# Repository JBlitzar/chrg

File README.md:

# chrg

chrg is a usbc charging hub. You can use it to charge your devices! It uses a CH224K PD sink as input, and then 4xIP6518 PD source controllers as output. 

Thanks to the IP6518, it should support:

 - 45W
 - USB-C Power Delivery
 - BC1.2 charging
 - Qualcomm QC2.0 and 3.0 charging
 - Apple, Huawei, Samsung, and Spreadtrum fast charging protocols
   - I don't have any huawei phones, but maybe you do! You can use chrg to charge them.

 Of course, YMMV when plugging in multiple devices. It's mostly bottlenecked by the wattage of your upstream brick (or alternatively 45W as the ip6518 spec says).

 ### Why I made this project

 I made this project because I like doing USB projects, and after making a [USB *data* hub](https://github.com/jblitzar/uhub), I thought it would be cool to make a *charging* hub. Plus, this way I can plug in one brick and charge my phone and headphones at the same time. I also think it's cool and was a way to learn a new chip (IP6518).

## Schematic

Root schematic:

Schematic for the `out` block:

## PCB

[View on Kicanvas](https://kicanvas.org/?repo=https%3A%2F%2Fgithub.com%2FJBlitzar%2Fchrg%2Ftree%2Fmain%2FPCB%2Fchrg)

## CAD

[Onshape link](https://cad.onshape.com/documents/9567810a3a804626e0b9bd5e/w/546991992eff6807c34164d7/e/56ab2d679f572004bdd7b5fb?renderMode=0&uiState=6a89de2326941f564e9ba193)

Assembly: [CAD/chrg_assembly.step](CAD/chrg_assembly.step)

Or just check the [CAD folder](CAD/)

PCB is held in place with the mounting holes

## How to use

### Assembly

Print chrg_case.step instead and slide it in from the side, like so:

Then the pins should keep it secure. 

### Usage

Plug a usbc laptop charger into the side port. Then, charge your devices from the front ports!

## Testimonials

Don't just take it from me! Hear what users are saying about chrg

> *What are you making...*

> *this shit is not passing tsa bro*

> *Scary*

> *CHAAARGGGGEEEEEEE!!!!!!!!!!!!!!*

## BOM

|Item                                              |link                               |Cost|Notes           |
|--------------------------------------------------|-----------------------------------|----|----------------|
|5x PCB (moq)                                      |N/A                                |4   |JLC             |
|2x PCBA (moq)                                     |N/A                                |45.87|JLC             |
|JLC shipping + taxes                              |N/A                                |8   |                |
|1x case                                           |N/A                                |0   |I can print this myself|
|Total                                             |N/A                                |57.87|                |

### Fabrication BOM

Other fabrication outputs at [PCB/chrg/production](PCB/chrg/production)

|Designator                                        |Footprint                          |Quantity|Value           |LCSC Part #|Link|
|--------------------------------------------------|-----------------------------------|--------|----------------|-----------|----|
|C1                                                |C0603                              |1       |1uf             |C15849     |[link](https://www.lcsc.com/product-detail/C15849.html)|
|C10, C11, C12, C13, C2, C3, C4, C5, C6, C7, C8, C9|C0603                              |12      |22uF            |C59461     |[link](https://www.lcsc.com/product-detail/C59461.html)|
|C14                                               |C1206                              |1       |100uF           |C15008     |[link](https://www.lcsc.com/product-detail/C15008.html)|
|C32, C34, C39, C41, C46, C48, C53, C55            |C0402                              |8       |100nF           |C1525      |[link](https://www.lcsc.com/product-detail/C1525.html)|
|C33, C40, C47, C54                                |C0402                              |4       |1nF             |C1523      |[link](https://www.lcsc.com/product-detail/C1523.html)|
|F1                                                |FUSE-SMD_2410-T4A-125V             |1       |4A fuse         |C5220739   |[link](https://www.lcsc.com/product-detail/C5220739.html)|
|L1, L2, L3, L4                                    |IND-SMD_L14.4-W12.8                |4       |SLO1350H220MTT  |C364085    |[link](https://www.lcsc.com/product-detail/C364085.html)|
|LED1, LED6, LED7, LED8, LED9                      |LED0805-R-RD                       |5       |0805G           |C2297      |[link](https://www.lcsc.com/product-detail/C2297.html)|
|R16, R17, R19, R20, R21, R22, R23, R25, R26       |R0402                              |9       |3.3kΩ           |C25890     |[link](https://www.lcsc.com/product-detail/C25890.html)|
|R2                                                |R0402                              |1       |1k              |C11702     |[link](https://www.lcsc.com/product-detail/C11702.html)|
|R3, R4, R5, R6                                    |R0603                              |4       |2Ω              |C22977     |[link](https://www.lcsc.com/product-detail/C22977.html)|
|U1                                                |R0805                              |1       |10k             |C17414     |[link](https://www.lcsc.com/product-detail/C17414.html)|
|U11, U13, U15, U17                                |QFN-24_L4.0-W4.0-P0.50-BL-EP2.6    |4       |IP6518          |C181688    |[link](https://www.lcsc.com/product-detail/C181688.html)|
|U2                                                |ESSOP-10_L4.9-W3.9-P1.0-LS6.0-TL-EP|1       |CH224K          |C970725    |[link](https://www.lcsc.com/product-detail/C970725.html)|
|USB1, USB10, USB11, USB12, USB9                   |USB-C-SMD_TYPE-C-16PIN-2MD-073     |5       |TYPE-C 16PIN 2MD|C2765186   |[link](https://www.lcsc.com/product-detail/C2765186.html)|

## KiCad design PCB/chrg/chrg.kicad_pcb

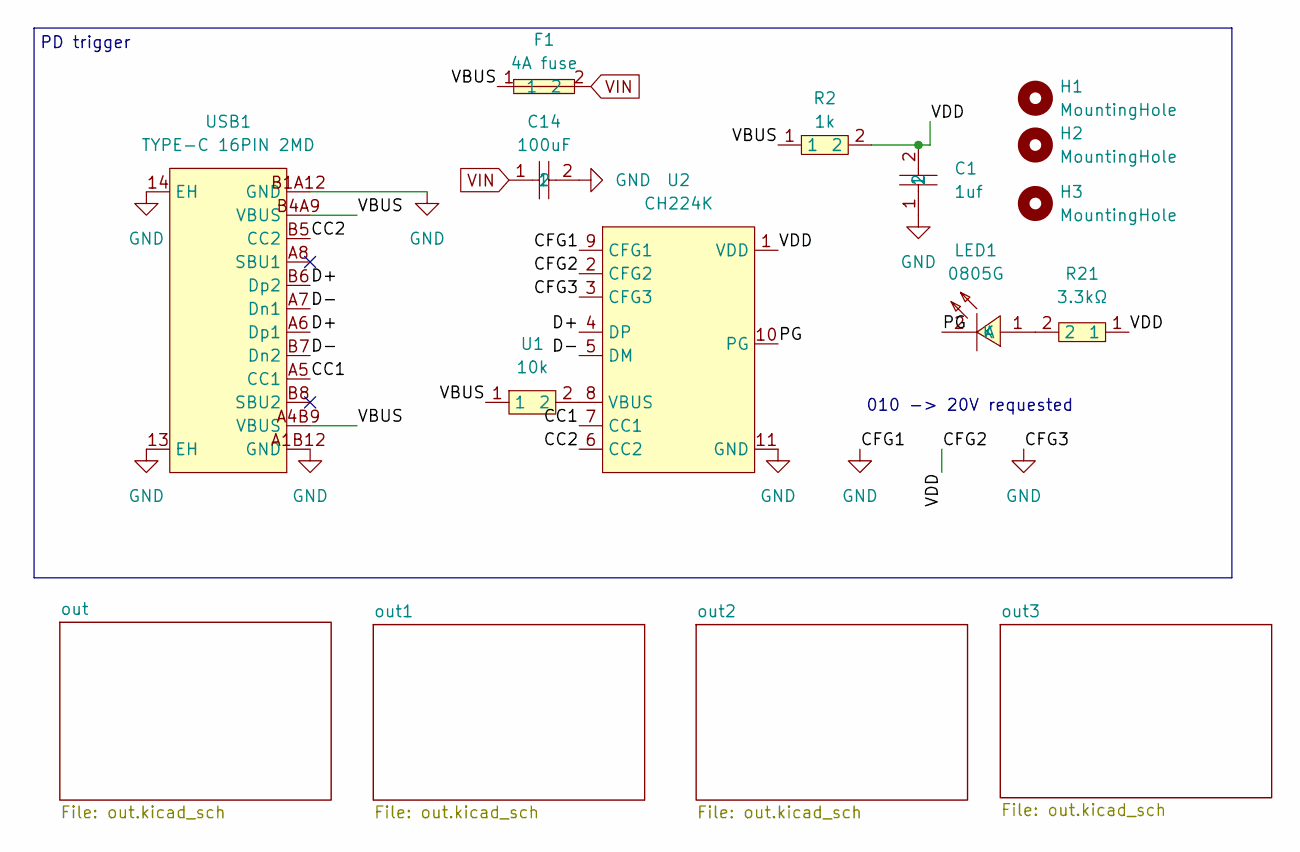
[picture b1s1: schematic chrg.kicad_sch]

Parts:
C1: 1uf; C0603; MPN CL10A105KB8NNNC; LCSC Part C15849
C14: 100uF; C1206; MPN CL31A107MQHNNNE; LCSC Part C15008
F1: 4A fuse; FUSE-SMD_2410-T4A-125V; MPN 2410 T4A/125V; LCSC Part C5220739
H1, H2, H3: MountingHole; MountingHole_2.2mm_M2
LED1: 0805G; LED0805-R-RD; MPN KT-0805G; LCSC Part C2297
R2: 1k; R0402; MPN 0402WGF1001TCE; LCSC Part C11702
R21: 3.3kΩ; R0402; MPN 0402WGF3301TCE; LCSC Part C25890
U1: 10k; R0805; MPN 0805W8F1002T5E; LCSC Part C17414
U2: CH224K; ESSOP-10_L4.9-W3.9-P1.0-LS6.0-TL-EP; MPN CH224K; LCSC Part C970725
USB1: TYPE-C 16PIN 2MD; USB-C-SMD_TYPE-C-16PIN-2MD-073; MPN TYPE-C 16PIN 2MD(073); LCSC Part C2765186

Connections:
/CC1: U2.7 (CC1), USB1.A5 (CC1)
/CC2: U2.6 (CC2), USB1.B5 (CC2)
/CFG2: C1.2, R2.2, R21.1, U2.1 (VDD), U2.2 (CFG2)
/D+: U2.4 (DP), USB1.A6 (Dp1), USB1.B6 (Dp2)
/D-: U2.5 (DM), USB1.A7 (Dn1), USB1.B7 (Dn2)
/PG: LED1.2 (K), U2.10 (PG)
/VBUS: F1.1, R2.1, U1.1, USB1.A4B9 (VBUS), USB1.B4A9 (VBUS)
GND: C1.1, C14.2, U2.3 (CFG3), U2.9 (CFG1), U2.11 (GND), USB1.13 (EH), USB1.14 (EH), USB1.A1B12 (GND), USB1.B1A12 (GND); also elsewhere on the board
unnamed: LED1.1 (A), R21.2
unnamed: U1.2, U2.8 (VBUS)
VIN: C14.1, F1.2; also elsewhere on the board

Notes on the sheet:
PD trigger
010 -> 20V requested

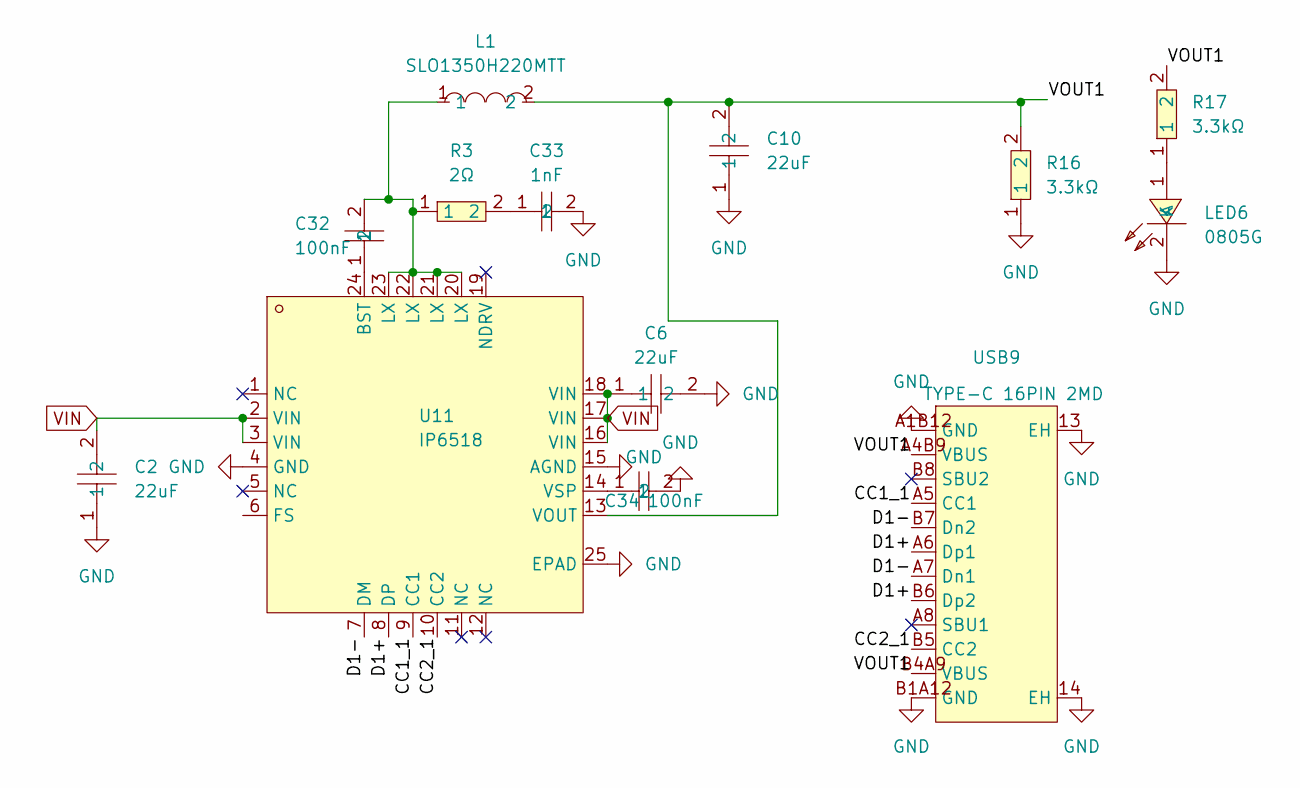
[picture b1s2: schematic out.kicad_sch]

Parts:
C2, C6, C10: 22uF; C0603; MPN CL10A226MQ8NRNC; LCSC Part C59461
C32, C34: 100nF; C0402; MPN CL05B104KO5NNNC; LCSC Part C1525
C33: 1nF; C0402; MPN 0402B102K500NT; LCSC Part C1523
L1: SLO1350H220MTT; IND-SMD_L14.4-W12.8; MPN SLO1350H220MTT; LCSC Part C364085
LED6: 0805G; LED0805-R-RD; MPN KT-0805G; LCSC Part C2297
R3: 2Ω; R0603; MPN 0603WAF200KT5E; LCSC Part C22977
R16, R17: 3.3kΩ; R0402; MPN 0402WGF3301TCE; LCSC Part C25890
U11: IP6518; QFN-24_L4.0-W4.0-P0.50-BL-EP2.6; MPN IP6518; LCSC Part C181688
USB9: TYPE-C 16PIN 2MD; USB-C-SMD_TYPE-C-16PIN-2MD-073; MPN TYPE-C 16PIN 2MD(073); LCSC Part C2765186

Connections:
/out/CC1_1: U11.9 (CC1), USB9.A5 (CC1)
/out/CC2_1: U11.10 (CC2), USB9.B5 (CC2)
/out/D1+: U11.8 (DP), USB9.A6 (Dp1), USB9.B6 (Dp2)
/out/D1-: U11.7 (DM), USB9.A7 (Dn1), USB9.B7 (Dn2)
/out/VOUT1: C10.2, L1.2, R16.2, R17.2, U11.13 (VOUT), USB9.A4B9 (VBUS), USB9.B4A9 (VBUS)
GND: C2.1, C6.2, C10.1, C33.2, C34.2, LED6.2 (K), R16.1, U11.4 (GND), U11.15 (AGND), U11.25 (EPAD), USB9.13 (EH), USB9.14 (EH), USB9.A1B12 (GND), USB9.B1A12 (GND); also elsewhere on the board
unnamed: C32.2, L1.1, R3.1, U11.20 (LX), U11.21 (LX), U11.22 (LX), U11.23 (LX)
unnamed: C33.1, R3.2
unnamed: LED6.1 (A), R17.1
unnamed: C32.1, U11.24 (BST)
unnamed: C34.1, U11.14 (VSP)
VIN: C2.2, C6.1, U11.2 (VIN), U11.3 (VIN), U11.16 (VIN), U11.17 (VIN), U11.18 (VIN); also elsewhere on the board

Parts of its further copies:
C3, C4, C5, C7, C8, C9, C11, C12, C13: 22uF; C0603; MPN CL10A226MQ8NRNC; LCSC Part C59461
C39, C41, C46, C48, C53, C55: 100nF; C0402; MPN CL05B104KO5NNNC; LCSC Part C1525
C40, C47, C54: 1nF; C0402; MPN 0402B102K500NT; LCSC Part C1523
L2, L3, L4: SLO1350H220MTT; IND-SMD_L14.4-W12.8; MPN SLO1350H220MTT; LCSC Part C364085
LED7, LED8, LED9: 0805G; LED0805-R-RD; MPN KT-0805G; LCSC Part C2297
R4, R5, R6: 2Ω; R0603; MPN 0603WAF200KT5E; LCSC Part C22977
R19, R20, R22, R23, R25, R26: 3.3kΩ; R0402; MPN 0402WGF3301TCE; LCSC Part C25890
U13, U15, U17: IP6518; QFN-24_L4.0-W4.0-P0.50-BL-EP2.6; MPN IP6518; LCSC Part C181688
USB10, USB11, USB12: TYPE-C 16PIN 2MD; USB-C-SMD_TYPE-C-16PIN-2MD-073; MPN TYPE-C 16PIN 2MD(073); LCSC Part C2765186

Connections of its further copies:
/out1/CC1_1: U13.9 (CC1), USB10.A5 (CC1)
/out1/CC2_1: U13.10 (CC2), USB10.B5 (CC2)
/out1/D1+: U13.8 (DP), USB10.A6 (Dp1), USB10.B6 (Dp2)
/out1/D1-: U13.7 (DM), USB10.A7 (Dn1), USB10.B7 (Dn2)
/out1/VOUT1: C11.2, L2.2, R19.2, R20.2, U13.13 (VOUT), USB10.A4B9 (VBUS), USB10.B4A9 (VBUS)
/out2/CC1_1: U15.9 (CC1), USB11.A5 (CC1)
/out2/CC2_1: U15.10 (CC2), USB11.B5 (CC2)
/out2/D1+: U15.8 (DP), USB11.A6 (Dp1), USB11.B6 (Dp2)
/out2/D1-: U15.7 (DM), USB11.A7 (Dn1), USB11.B7 (Dn2)
/out2/VOUT1: C12.2, L3.2, R22.2, R23.2, U15.13 (VOUT), USB11.A4B9 (VBUS), USB11.B4A9 (VBUS)
/out3/CC1_1: U17.9 (CC1), USB12.A5 (CC1)
/out3/CC2_1: U17.10 (CC2), USB12.B5 (CC2)
/out3/D1+: U17.8 (DP), USB12.A6 (Dp1), USB12.B6 (Dp2)
/out3/D1-: U17.7 (DM), USB12.A7 (Dn1), USB12.B7 (Dn2)
/out3/VOUT1: C13.2, L4.2, R25.2, R26.2, U17.13 (VOUT), USB12.A4B9 (VBUS), USB12.B4A9 (VBUS)
GND: C3.1, C4.1, C5.1, C7.2, C8.2, C9.2, C11.1, C12.1, C13.1, C40.2, C41.2, C47.2, C48.2, C54.2, C55.2, LED7.2 (K), LED8.2 (K), LED9.2 (K), R19.1, R22.1, R25.1, U13.4 (GND), U13.15 (AGND), U13.25 (EPAD), U15.4 (GND), U15.15 (AGND), U15.25 (EPAD), U17.4 (GND), U17.15 (AGND), U17.25 (EPAD), USB10.13 (EH), USB10.14 (EH), USB10.A1B12 (GND), USB10.B1A12 (GND), USB11.13 (EH), USB11.14 (EH), USB11.A1B12 (GND), USB11.B1A12 (GND), USB12.13 (EH), USB12.14 (EH), USB12.A1B12 (GND), USB12.B1A12 (GND); also elsewhere on the board
unnamed: C39.2, L2.1, R4.1, U13.20 (LX), U13.21 (LX), U13.22 (LX), U13.23 (LX)
unnamed: C40.1, R4.2
unnamed: C46.2, L3.1, R5.1, U15.20 (LX), U15.21 (LX), U15.22 (LX), U15.23 (LX)
unnamed: C47.1, R5.2
unnamed: C53.2, L4.1, R6.1, U17.20 (LX), U17.21 (LX), U17.22 (LX), U17.23 (LX)
unnamed: C54.1, R6.2
unnamed: LED7.1 (A), R20.1
unnamed: LED8.1 (A), R23.1
unnamed: LED9.1 (A), R26.1
unnamed: C39.1, U13.24 (BST)
unnamed: C41.1, U13.14 (VSP)
unnamed: C46.1, U15.24 (BST)
unnamed: C48.1, U15.14 (VSP)
unnamed: C53.1, U17.24 (BST)
unnamed: C55.1, U17.14 (VSP)
VIN: C3.2, C4.2, C5.2, C7.1, C8.1, C9.1, U13.2 (VIN), U13.3 (VIN), U13.16 (VIN), U13.17 (VIN), U13.18 (VIN), U15.2 (VIN), U15.3 (VIN), U15.16 (VIN), U15.17 (VIN), U15.18 (VIN), U17.2 (VIN), U17.3 (VIN), U17.16 (VIN), U17.17 (VIN), U17.18 (VIN); also elsewhere on the board

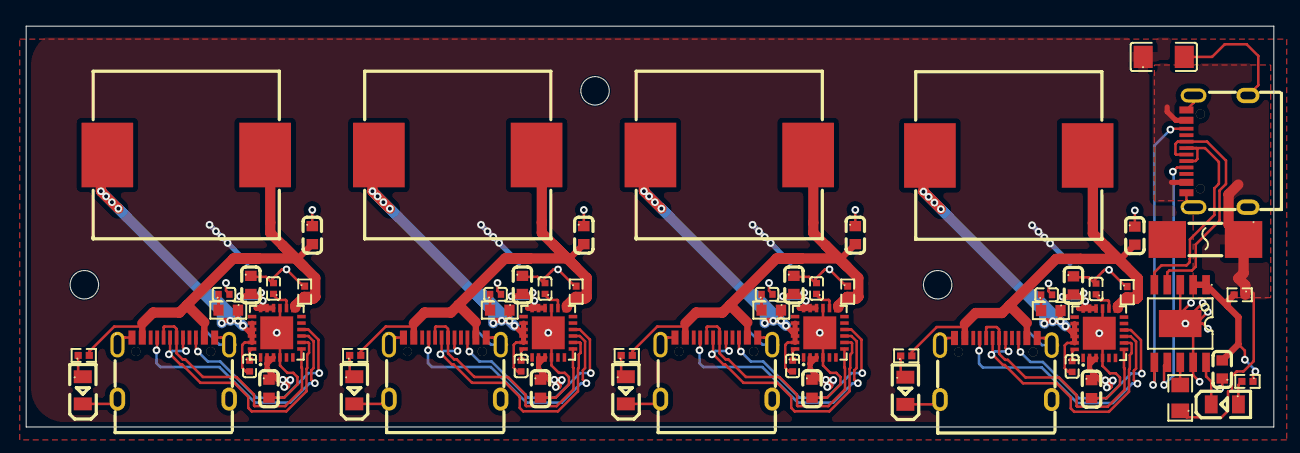
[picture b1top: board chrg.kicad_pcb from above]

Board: 2 copper layers, 96.5 x 31.0 mm, 65 parts (1 on the bottom side), 51 nets.

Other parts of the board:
kobee-studio-6A88F8E8: Kobee Studio; kobee-studio-6A88F8A7

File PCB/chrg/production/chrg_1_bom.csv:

Designator,Footprint,Quantity,Value,LCSC Part #
C1,C0603,1,1uf,C15849
"C10, C11, C12, C13, C2, C3, C4, C5, C6, C7, C8, C9",C0603,12,22uF,C59461
C14,C1206,1,100uF,C15008
"C32, C34, C39, C41, C46, C48, C53, C55",C0402,8,100nF,C1525
"C33, C40, C47, C54",C0402,4,1nF,C1523
F1,FUSE-SMD_2410-T4A-125V,1,4A fuse,C5220739
"L1, L2, L3, L4",IND-SMD_L14.4-W12.8,4,SLO1350H220MTT,C364085
"LED1, LED6, LED7, LED8, LED9",LED0805-R-RD,5,0805G,C2297
"R16, R17, R19, R20, R21, R22, R23, R25, R26",R0402,9,3.3kΩ,C25890
R2,R0402,1,1k,C11702
"R3, R4, R5, R6",R0603,4,2Ω,C22977
U1,R0805,1,10k,C17414
"U11, U13, U15, U17",QFN-24_L4.0-W4.0-P0.50-BL-EP2.6,4,IP6518,C181688
U2,ESSOP-10_L4.9-W3.9-P1.0-LS6.0-TL-EP,1,CH224K,C970725
"USB1, USB10, USB11, USB12, USB9",USB-C-SMD_TYPE-C-16PIN-2MD-073,5,TYPE-C 16PIN 2MD,C2765186
